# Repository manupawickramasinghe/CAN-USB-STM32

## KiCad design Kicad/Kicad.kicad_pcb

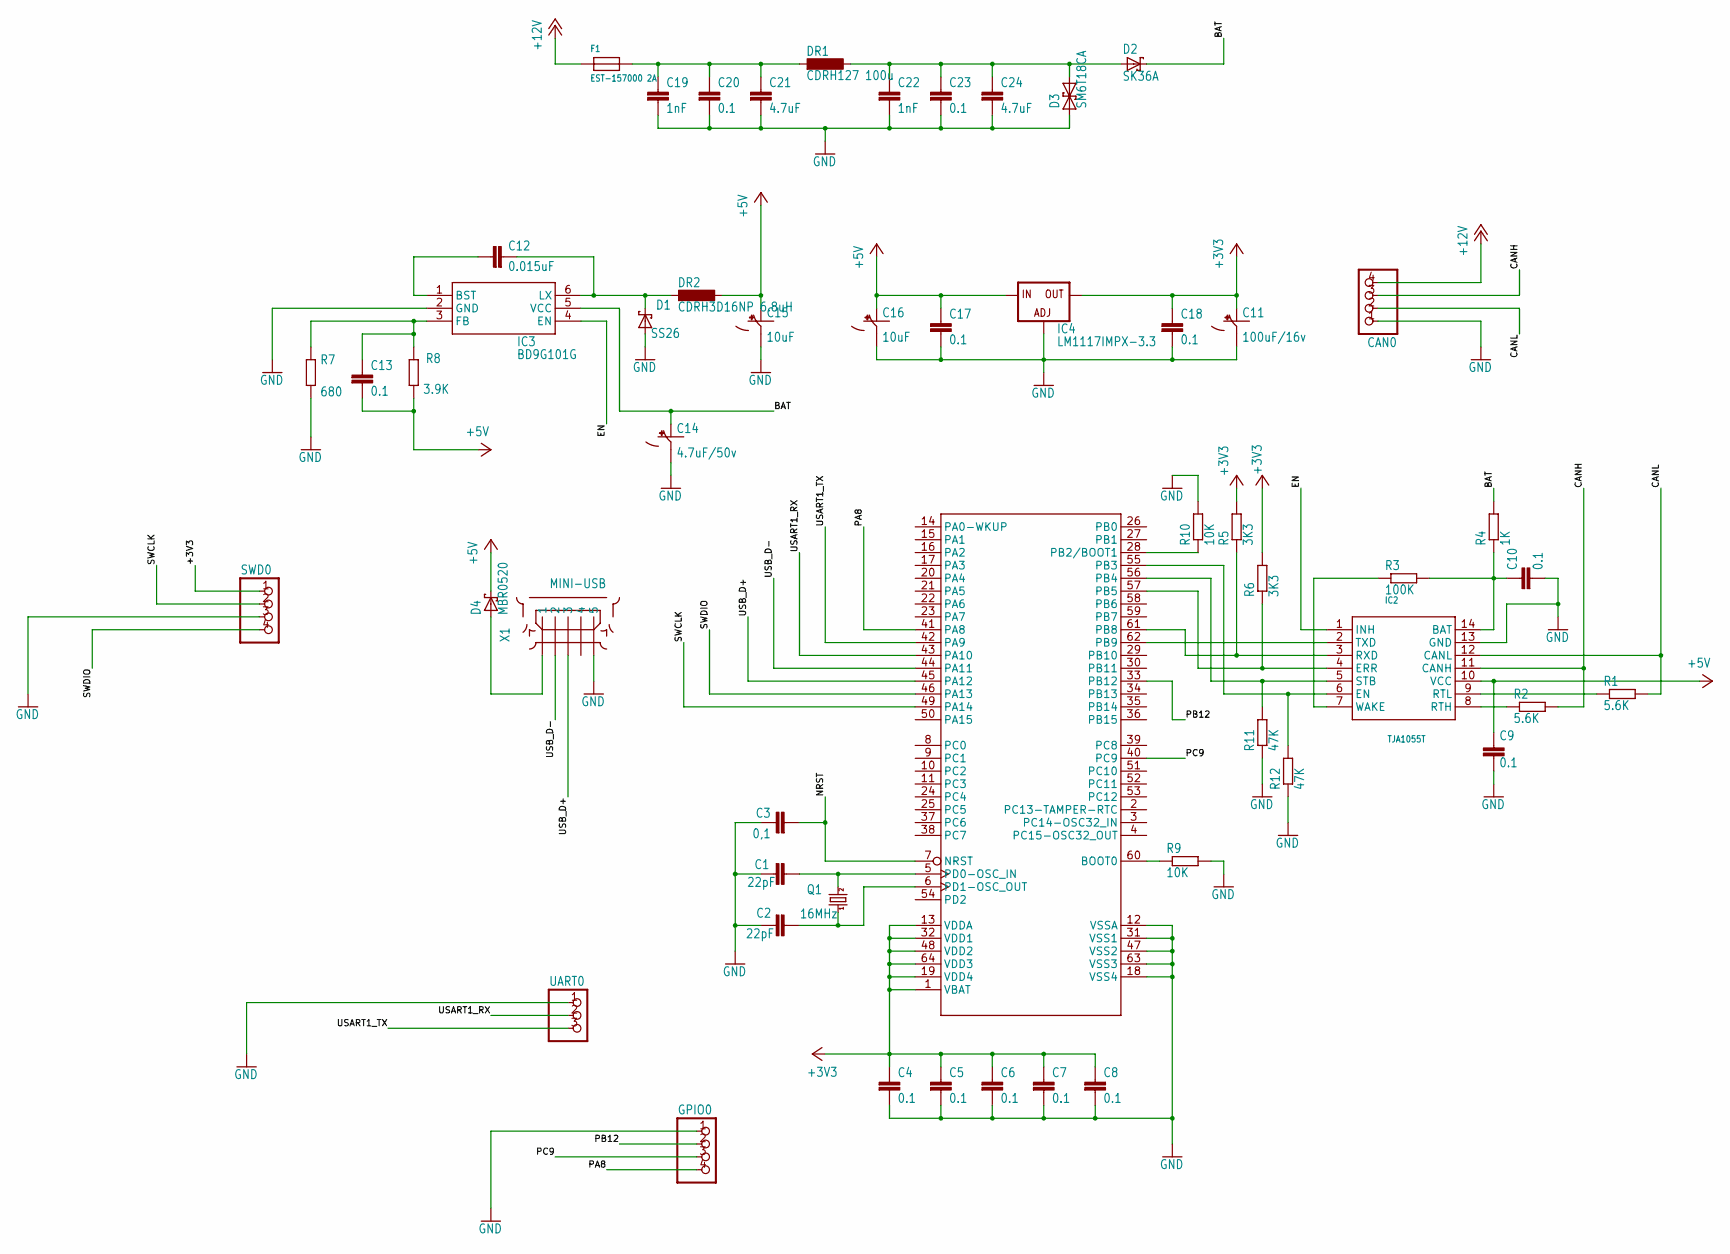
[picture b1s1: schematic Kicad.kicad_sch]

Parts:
C1, C2: 22pF; C0805
C3: 0,1; C0805
C4, C5, C6, C7, C8, C9, C10, C13, C17, C18, C20, C23: 0.1; C0805
C11: 100uF/16v; 153CLV-0605
C12: 0.015uF; C0805
C14: 4.7uF/50v; 153CLV-0605
C15, C16: 10uF; 153CLV-0605
C19, C22: 1nF; C0805
C21, C24: 4.7uF; C0805
CAN0: PINHD-1X4; 1X04
D1: SS26; SMB
D2: SK36A; DO-214AC
D3: SM6T18CA; DO214AA
D4: MBR0520; SOD123
DR1: CDRH127 100u; MS85
DR2: CDRH3D16NP 6.8uH; CDRH3D16NP
F1: EST-157000 2A; FUSE
GPIO0: PINHD-1X4; 1X04
IC1: STM32F105RT; LQFP64
IC2: TJA1055T; SO-14W
IC3: BD9G101G; SSOP6
IC4: LM1117IMPX-3.3; SOT223
Q1: 16MHz; HC49UP
R1, R2: 5.6K; R0805
R3: 100K; R0805
R4: 1K; R0805
R5, R6: 3K3; R0805
R7: 680; R0805
R8: 3.9K; R0805
R9, R10: 10K; R0805
R11, R12: 47K; R0805
SWD0: PINHD-1X4; 1X04
UART0: PINHD-1X3; 1X03
X1: MINI-USB; UX60-MB-5ST

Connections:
+3V3: C4.1, C5.1, C6.1, C7.1, C8.1, C11.+, C18.1, IC1.1 (VBAT), IC1.13 (VDDA), IC1.19 (VDD4), IC1.32 (VDD1), IC1.48 (VDD2), IC1.64 (VDD3), IC4.2 (OUT), IC4.4 (OUT), R5.2, R6.2, SWD0.1
+5V: C9.1, C13.2, C15.+, C16.+, C17.1, D4.C, DR2.P$2 (2), IC2.10 (VCC), IC4.3 (IN), R8.1
+12V: CAN0.4, F1.P$1 (1)
BAT: C14.+, D2.C, IC3.5 (VCC), R4.2
CANH: CAN0.3, IC2.11 (CANH), R2.2
CANL: CAN0.2, IC2.12 (CANL), R1.2
EN: IC2.1 (INH), IC3.4 (EN)
GND: C1.2, C2.2, C3.1, C4.2, C5.2, C6.2, C7.2, C8.2, C9.2, C10.2, C11.-, C14.-, C15.-, C16.-, C17.2, C18.2, C19.2, C20.2, C21.2, C22.2, C23.2, C24.2, CAN0.1, D1.A, D3.A (1), GPIO0.1, IC1.12 (VSSA), IC1.18 (VSS4), IC1.31 (VSS1), IC1.47 (VSS2), IC1.63 (VSS3), IC2.13 (GND), IC3.2 (GND), IC4.1 (ADJ), R7.1, R9.2, R10.2, R11.1, R12.1, SWD0.3, UART0.1, X1.5, X1.M1 (5), X1.M2 (5)
unnamed: C1.1, IC1.5 (PD0-OSC_IN), Q1.2
unnamed: C2.1, IC1.6 (PD1-OSC_OUT), Q1.1
unnamed: IC1.60 (BOOT0), R9.1
unnamed: IC1.61 (PB8), IC2.3 (RXD), R5.1
unnamed: IC1.62 (PB9), IC2.2 (TXD)
unnamed: IC1.56 (PB4), IC2.5 (STB), R11.2
unnamed: IC2.8 (RTH), R2.1
unnamed: IC2.9 (RTL), R1.1
unnamed: C12.1, IC3.1 (BST)
unnamed: IC2.7 (WAKE), R3.1
unnamed: C10.1, IC2.14 (BAT), R3.2, R4.1
unnamed: C12.2, D1.C, DR2.P$1 (1), IC3.6 (LX)
unnamed: C13.1, IC3.3 (FB), R7.2, R8.2
unnamed: IC1.55 (PB3), IC2.6 (EN), R12.2
unnamed: IC1.57 (PB5), IC2.4 (ERR), R6.1
unnamed: IC1.28 (PB2/BOOT1), R10.1
unnamed: C22.1, C23.1, C24.1, D2.A, D3.C (2), DR1.P$2 (2)
unnamed: C19.1, C20.1, C21.1, DR1.P$1 (1), F1.P$2 (2)
unnamed: D4.A, X1.1
NRST: C3.2, IC1.7 (NRST)
PA8: GPIO0.4, IC1.41 (PA8)
PB12: GPIO0.2, IC1.33 (PB12)
PC9: GPIO0.3, IC1.40 (PC9)
SWCLK: IC1.49 (PA14), SWD0.2
SWDIO: IC1.46 (PA13), SWD0.4
USART1_RX: IC1.43 (PA10), UART0.2
USART1_TX: IC1.42 (PA9), UART0.3
USB_D+: IC1.45 (PA12), X1.3
USB_D-: IC1.44 (PA11), X1.2

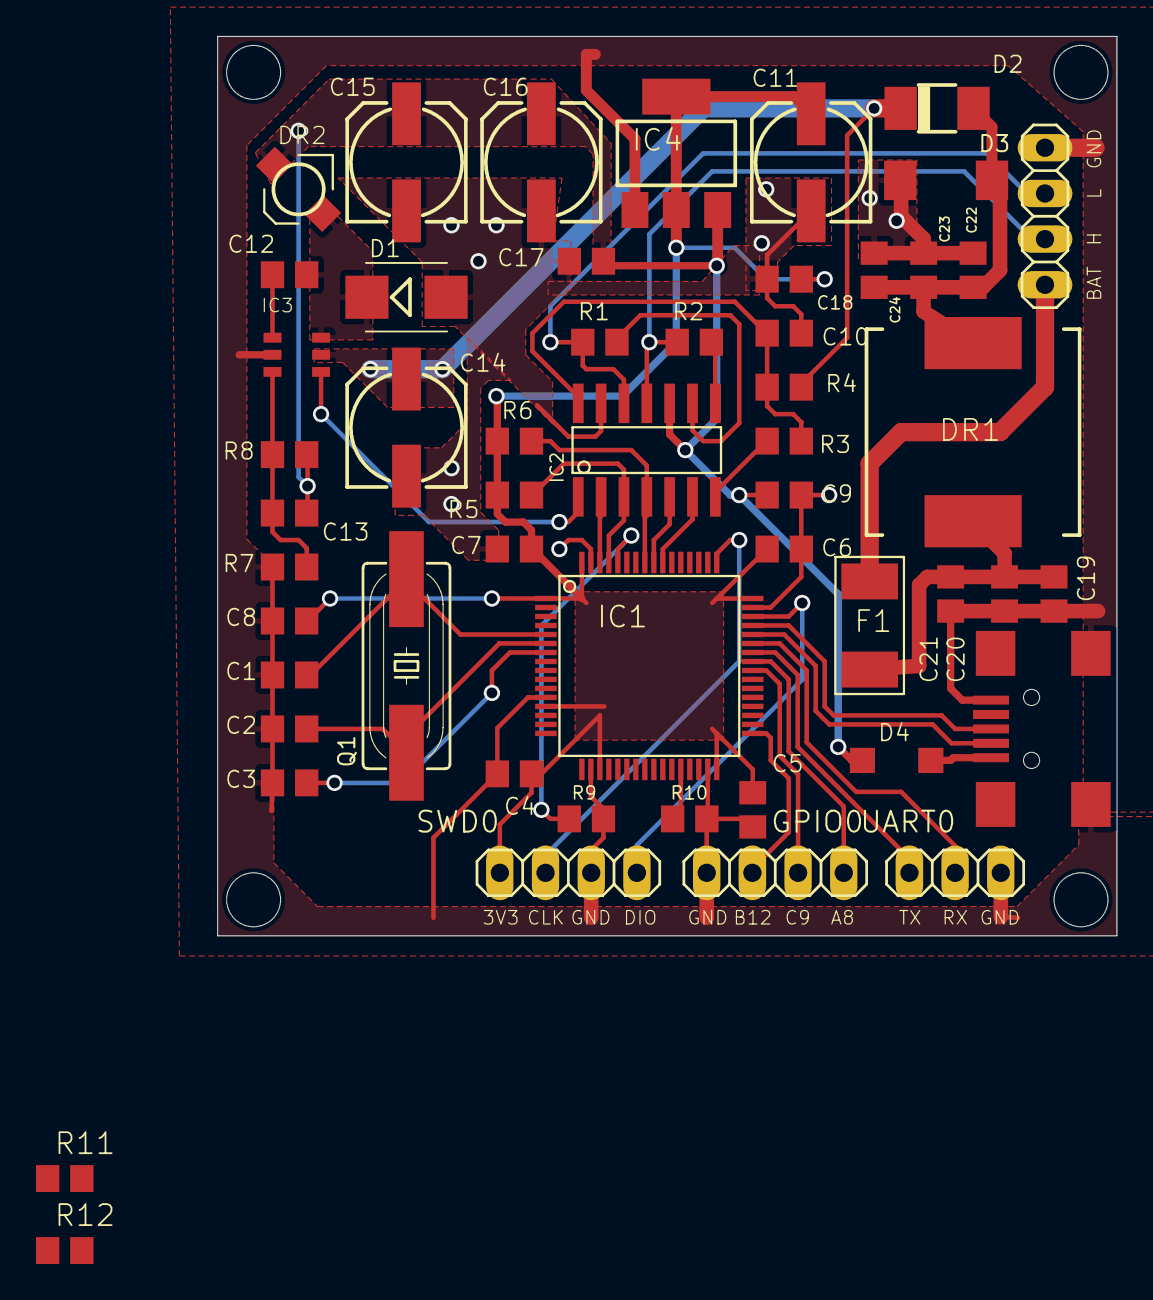
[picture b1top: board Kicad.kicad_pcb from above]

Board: 2 copper layers, 50.0 x 50.0 mm, 57 parts (0 on the bottom side), 37 nets.

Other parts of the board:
UNK_HOLE_0: dummyfp0
UNK_HOLE_1: dummyfp1
UNK_HOLE_2: dummyfp2
UNK_HOLE_3: dummyfp3

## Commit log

2025-03-29 Kicad Exports
